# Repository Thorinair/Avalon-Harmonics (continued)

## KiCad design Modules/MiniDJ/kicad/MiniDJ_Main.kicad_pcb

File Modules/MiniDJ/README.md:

# Avalon Harmonics MiniDJ

**Stereo crossfader and DJ style filter**

MiniDJ is a compact fully analog module that houses a stereo crossfader with an adjustable volume curve, as well as a DJ style filter, both adjustable with CV. The module is compact at only 6hp and very shallow, making it an easy install in various travel and performance cases. **Features a golden (ENIG coated) panel.**

The module has two sets of stereo inputs, which correspond to channels A and B, as well as a stereo output. The two channels are mixed together through the crossfader, and are then passed into the DJ style filter before leaving the module.

Crossfader is controlled using the FADE knob. A switch just below the knob adjusts the volume curve between logarihtmic when flipped to the left or linear when flipped to the right. Logarithmic curve is more popular among DJs, while the linear curve is a more standard shape in passive crossfaders. The crossfade can also be controlled using CV through the FADE jack. An input of -5V will give 100% A channel, while an input of +5V will give 100% B channel. The FADE knob can be used as an offset when using the CV input.

Output of the crossfader is fed into the DJ style filter. The filter is based on Thomas Henry's VCF circuit, but modified to fit this use case. Cutoff is controlled using the CUT knob. The knob has a center detent for easier live performance. This is where the filter is completely open. As the knob is turned to the left, the signal gets lowpassed. As the knob is turned to the right, the signal gets highpassed. Resonances of LP and HP are controlled separately using the two RES knobs. Note that the filter itself is always active even when in neutral position, so resonance adds some coloration to the sound. Because of this, resonance knobs can be used as a sort of equalizer for the overall sound, even when the cutoff is in neutral position. Cutoff can also be controlled using CV through the CUT jack. An input of -5V will fully lowpass it, while an input of +5V will fully highpass it. Similar to the crossfader, the CUT knob can be used as an offset when using the CV input.

Finally, the module also has a set of two red LEDs which flash when clipping is expected on the output. Internally, the module halves the volume of both channels to prevent internal clipping, and then boosts it back up on output. Some clipping can occur though when mixing two loud signals together or when high resonance is involved. The LEDs help in those cases.

Visit Website: https://avalon-harmonics.com/module/MiniDJ/

### Features

* Stereo crossfader with adjustable curve
* Stereo DJ style filter
* Separate LP and HP resonances
* CV inputs for crossfader and filter
* Fully analog circuitry
* Clipping LEDs for output
* Wrong polarity protection
* Skiff friendly
* Size: 6HP
* Depth: 26mm
* Power: +12V: 93mA, -12V: 89mA

### Credits

* Filter circuit based on [Thomas Henry's VCF circuit](https://www.birthofasynth.com/Thomas_Henry/Pages/VCF-1.html)

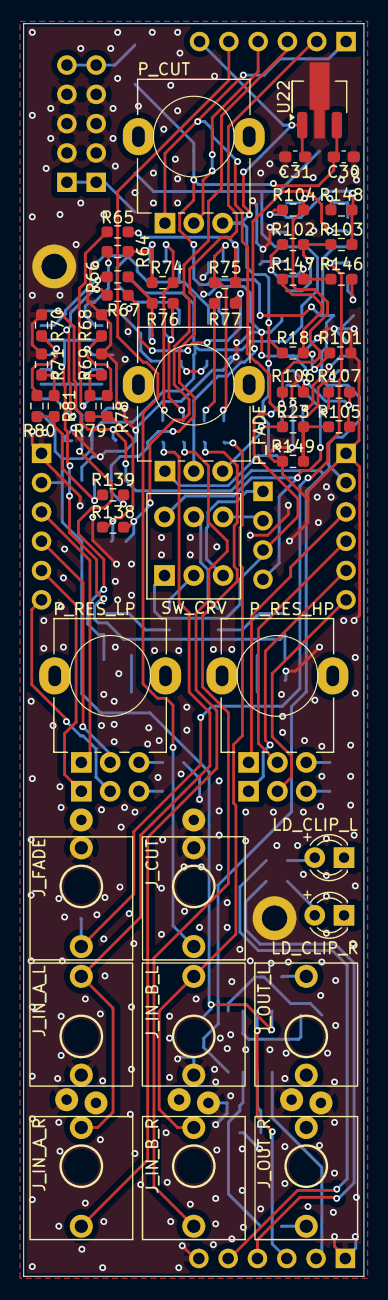
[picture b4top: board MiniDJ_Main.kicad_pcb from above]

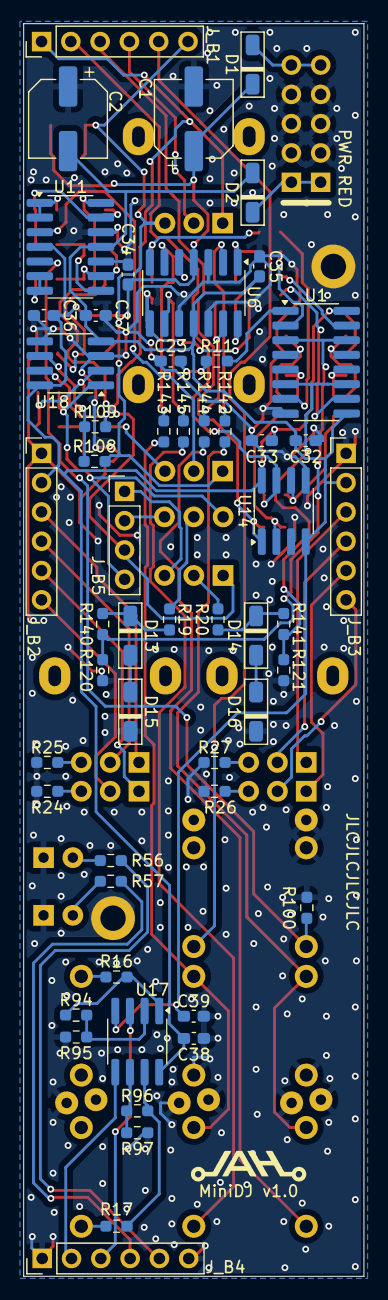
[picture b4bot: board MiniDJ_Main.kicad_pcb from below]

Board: 2 copper layers, 29.5 x 108.6 mm, 104 parts (55 on the bottom side), 82 nets.

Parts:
C1, C2: 47uF; CP_Elec_6.3x5.3
C23: 4.7nF; C_0603_1608Metric_Pad1.08x0.95mm_HandSolder
C30, C31, C32, C33, C34, C35, C36, C37, C38, C39: 0.1uF; C_0603_1608Metric_Pad1.08x0.95mm_HandSolder
D1, D2: FM4001; D_SOD-123F_AH
D13, D14: BZT52C4V3 (4.3V); D_SOD-123F_AH
D15, D16: BZT52C2V0 (2.0V); D_SOD-123F_AH
J_B1, J_B2, J_B3, J_B4: Conn_01x06_Female; PinHeader_1x06_P2.54mm_Vertical
J_B5: Conn_01x04_Female; PinHeader_1x04_P2.54mm_Vertical
J_CUT: PJ301M-12
J_FADE: PJ301M-12
J_IN_A_L: PJ301M-12; PJ301M-12 Offset
J_IN_A_R: PJ301M-12; PJ301M-12 Offset
J_IN_B_L: PJ301M-12; PJ301M-12 Offset
J_IN_B_R: PJ301M-12; PJ301M-12 Offset
J_OUT_L: PJ301M-12; PJ301M-12 Offset
J_OUT_R: PJ301M-12; PJ301M-12 Offset
LD_CLIP_L: LED; LED_D3.0mm_FlatTop
LD_CLIP_R: LED; LED_D3.0mm_FlatTop
PWR1: PWR_10_Pin; Eurorack Power 10 Pin
P_CUT: B50k; Potentiometer Alpha RD901F-40-00D
P_FADE: B100k; Potentiometer Alpha RD901F-40-00D
P_RES_HP: B50k; Potentiometer Alpha Dual RD901F-40-00D
P_RES_LP: B50k; Potentiometer Alpha Dual RD901F-40-00D
R11: 100; R_0603_1608Metric_Pad0.98x0.95mm_HandSolder
R16, R17, R18, R19, R20: 1k; R_0603_1608Metric_Pad0.98x0.95mm_HandSolder
R23: 2.7k; R_0603_1608Metric_Pad0.98x0.95mm_HandSolder
R24, R25, R26, R27: 5.6k; R_0603_1608Metric_Pad0.98x0.95mm_HandSolder
R56, R57: 22k; R_0603_1608Metric_Pad0.98x0.95mm_HandSolder
R64, R65, R66, R67, R68, R69, R70, R71: 47k; R_0603_1608Metric_Pad0.98x0.95mm_HandSolder
R74, R75, R76, R77, R78, R79, R80, R81, R94, R95, R96, R97, R100, R101, R102, R103, R104, R105, R106, R107, R108, R109, R120, R121: 100k; R_0603_1608Metric_Pad0.98x0.95mm_HandSolder
R138, R139, R140, R141: 160k; R_0603_1608Metric_Pad0.98x0.95mm_HandSolder
R142, R143, R144, R145, R146, R147, R148, R149: 200k; R_0603_1608Metric_Pad0.98x0.95mm_HandSolder
SW_CRV: SW_DPDT_x2; DPDT
U1: AS3364D; SO-16_3.9x9.9mm_P1.27mm_AH
U6, U11: TL074; SO-14_3.9x8.65mm_P1.27mm_AH
U14, U17, U18: TL072; SO-8_3.9x4.9mm_P1.27mm_AH
U22: 78L05; SOT-89-3_Handsoldering

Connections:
+5V: C31.1, J_B1.6, P_CUT.3, P_FADE.1, R18.2, R108.2, U22.1 (VO)
+12V: C1.1, C30.1, C33.2, C34.1, C36.1, C38.1, D1.1 (K), J_B2.2, U1.16 (V+), U6.4 (V+), U11.4 (V+), U14.8 (V+), U17.8 (V+), U18.8 (V+), U22.3 (VI)
-5V: J_B1.1, P_CUT.1, P_FADE.3, R23.2, R109.1, U18.7
-12V: C2.2, C32.1, C35.2, C37.2, C39.2, D2.2 (A), J_B3.2, U1.9 (V-), U6.11 (V-), U11.11 (V-), U14.4 (V-), U17.4 (V-), U18.4 (V-)
/CLIP_L_MAIN: J_B4.5, R56.2
/CLIP_R_MAIN: J_B4.4, R57.2
/FADE_A: R120.2, R140.1, U1.3, U1.14
/FADE_A_LIN: J_B5.4, R107.1, SW_CRV.4 (A), U18.1
/FADE_A_LOG: J_B5.2, SW_CRV.6 (C)
/FADE_B: R121.2, R141.1, U1.6, U1.11
/FADE_B_LIN: J_B5.3, R104.1, R106.2, SW_CRV.1 (A), U11.14
/FADE_B_LOG: J_B5.1, SW_CRV.3 (C)
/IN_CUT_MAIN: J_B1.5, J_CUT.SIG
/IN_L_A: J_IN_A_L.SIG, J_IN_A_R.SW, R142.2
/IN_L_B: J_IN_B_L.SIG, J_IN_B_R.SW, R143.2
/MIX_L_MAIN: J_B1.3, R138.1, U14.1
/MIX_R_MAIN: J_B1.2, R139.1, U14.7
/PRE_L_MAIN: J_B4.3, U17.3 (+)
/PRE_R_MAIN: J_B4.2, U17.5 (+)
/P_CUT_MAIN: J_B1.4, P_CUT.2
/RES_HP_L_1_MAIN: J_B2.3, P_RES_HP.1
/RES_HP_L_2_MAIN: J_B2.4, P_RES_HP.2
/RES_HP_R_1_MAIN: J_B2.5, P_RES_HP.4
/RES_HP_R_2_MAIN: J_B2.6, P_RES_HP.5
/RES_LP_L_1_MAIN: J_B3.3, P_RES_LP.1
/RES_LP_L_2_MAIN: J_B3.4, P_RES_LP.2
/RES_LP_R_1_MAIN: J_B3.5, P_RES_LP.4
/RES_LP_R_2_MAIN: J_B3.6, P_RES_LP.5
GND: C1.2, C2.1, C23.2, C30.2, C31.2, C32.2, C33.1, C34.2, C35.1, C36.2, C37.1, C38.2, C39.1, D15.1 (K), D16.1 (K), J_B2.1, J_B3.1, J_B4.1, J_B4.6, J_CUT.GND, J_CUT.SW, J_FADE.GND, J_FADE.SW, J_IN_A_L.GND, J_IN_A_L.SW, J_IN_A_R.GND, J_IN_B_L.GND, J_IN_B_L.SW, J_IN_B_R.GND, J_OUT_L.GND, J_OUT_R.GND, LD_CLIP_L.1 (K), LD_CLIP_R.1 (K), PWR1.2 (GND), R24.1, R25.1, R26.1, R27.1, R68.1, R69.1, R70.1, R71.1, R95.1, R97.1, R100.1, R101.1, R120.1, R121.1, R149.1, U1.8 (GND), U6.3 (+), U6.5 (+), U6.10 (+), U6.12 (+), U11.10 (+), U11.12 (+), U14.3 (+), U14.5 (+), U18.3 (+), U18.5 (+), U22.2 (GND)
unnamed: C23.1, R11.2
unnamed: D1.2 (A), PWR1.1 (+12V)
unnamed: D2.1 (K), PWR1.3 (-12V)
unnamed: D13.2 (A), D15.2 (A)
unnamed: D13.1 (K), R19.1, R140.2
unnamed: D14.2 (A), D16.2 (A)
unnamed: D14.1 (K), R20.1, R141.2
unnamed: J_IN_A_R.SIG, R144.2
unnamed: J_IN_B_R.SIG, R145.2
unnamed: J_OUT_L.SIG, R16.1
unnamed: J_OUT_R.SIG, R17.1
unnamed: LD_CLIP_L.2 (A), R56.1
unnamed: LD_CLIP_R.2 (A), R57.1
unnamed: P_RES_HP.3, R25.2
unnamed: P_RES_HP.6, R24.2
unnamed: P_RES_LP.3, R27.2
unnamed: P_RES_LP.6, R26.2
unnamed: R16.2, R94.1, U17.1
unnamed: R17.2, R96.1, U17.7
unnamed: R64.1, U1.2
unnamed: R64.2, R74.1, U6.1
unnamed: R65.1, U1.7
unnamed: R65.2, R75.1, U6.7
unnamed: R66.1, U1.15
unnamed: R66.2, R76.1, U6.14
unnamed: R67.1, U1.10
unnamed: R67.2, R77.1, U6.8
unnamed: R68.2, R78.2, U1.4
unnamed: R69.2, R79.2, U1.5
unnamed: R70.2, R80.2, U1.13
unnamed: R71.2, R81.2, U1.12
unnamed: R18.1, R101.2, R147.2
unnamed: R102.1, R103.2, U11.8
unnamed: R23.1, R105.2, R149.2
unnamed: R20.2, SW_CRV.2 (B)
unnamed: R19.2, SW_CRV.5 (B)
unnamed: R11.1, U1.1 (Vref)
unnamed: R74.2, R142.1, U6.2 (-)
unnamed: R75.2, R143.1, U6.6 (-)
unnamed: R77.2, R145.1, U6.9 (-)
unnamed: R76.2, R144.1, U6.13 (-)
unnamed: P_FADE.2, U11.3 (+)
unnamed: R148.2, U11.1, U11.2 (-)
unnamed: J_FADE.SIG, R100.2, U11.5 (+)
unnamed: R146.2, U11.6 (-), U11.7
unnamed: R102.2, R146.1, R147.1, U11.9 (-)
unnamed: R103.1, R104.2, R148.1, U11.13 (-)
unnamed: R78.1, R79.1, R138.2, U14.2 (-)
unnamed: R80.1, R81.1, R139.2, U14.6 (-)
unnamed: R94.2, R95.2, U17.2 (-)
unnamed: R96.2, R97.2, U17.6 (-)
unnamed: R105.1, R106.1, R107.2, U18.2 (-)
unnamed: R108.1, R109.2, U18.6 (-)

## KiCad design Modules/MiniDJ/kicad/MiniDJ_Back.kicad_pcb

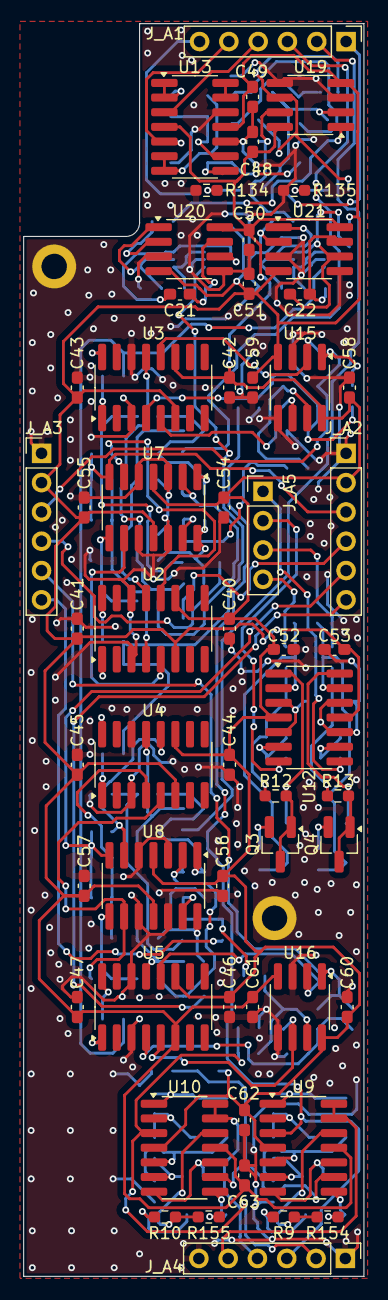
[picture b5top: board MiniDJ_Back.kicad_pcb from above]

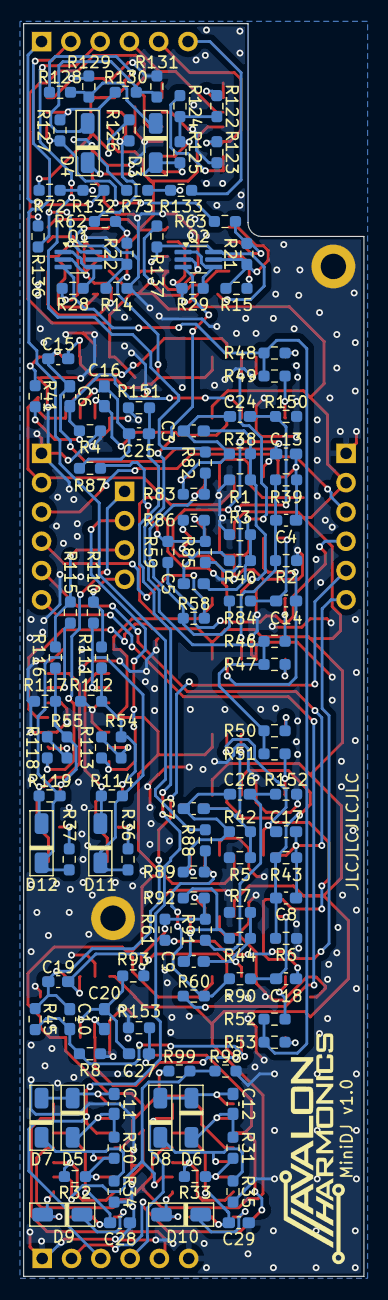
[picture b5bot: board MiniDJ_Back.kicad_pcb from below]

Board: 2 copper layers, 29.5 x 108.6 mm, 182 parts (126 on the bottom side), 115 nets.

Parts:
C3, C4, C5, C6, C7, C8, C9, C10: 10pF; C_0603_1608Metric_Pad1.08x0.95mm_HandSolder
C11, C12: 47pF; C_0603_1608Metric_Pad1.08x0.95mm_HandSolder
C13, C14, C15, C16, C17, C18, C19, C20: 330pF; C_0603_1608Metric_Pad1.08x0.95mm_HandSolder
C21, C22: 1nF; C_0603_1608Metric_Pad1.08x0.95mm_HandSolder
C24, C25, C26, C27, C28, C29, C40, C41, C42, C43, C44, C45, C46, C47, C48, C49, C50, C51, C52, C53, C54, C55, C56, C57, C58, C59, C60, C61, C62, C63: 0.1uF; C_0603_1608Metric_Pad1.08x0.95mm_HandSolder
D3, D4, D5, D6, D7, D8, D9, D10, D11, D12: 1N4148W; D_SOD-123F_AH
J_A1, J_A2, J_A3, J_A4: Conn_01x06_Male; PinHeader_1x06_P2.54mm_Vertical
J_A5: Conn_01x04_Male; PinHeader_1x04_P2.54mm_Vertical
Q1, Q2: BCM857BS; SOT-363_SC-70-6_Handsoldering
Q3, Q4: MMBT3906; SOT-23_Handsoldering
R1, R2, R3, R4, R5, R6, R7, R8: 22; R_0603_1608Metric_Pad0.98x0.95mm_HandSolder
R9, R10: 100; R_0603_1608Metric_Pad0.98x0.95mm_HandSolder
R12, R13: 220; R_0603_1608Metric_Pad0.98x0.95mm_HandSolder
R14, R15: 470; R_0603_1608Metric_Pad0.98x0.95mm_HandSolder
R21, R22: 2k; R_0603_1608Metric_Pad0.98x0.95mm_HandSolder
R28, R29: 5.6k; R_0603_1608Metric_Pad0.98x0.95mm_HandSolder
R30, R31, R32, R33, R34, R35, R36, R37: 10k; R_0603_1608Metric_Pad0.98x0.95mm_HandSolder
R38, R39, R40, R41, R42, R43, R44, R45: 11k; R_0603_1608Metric_Pad0.98x0.95mm_HandSolder
R46, R47, R48, R49, R50, R51, R52, R53, R54, R55: 15k; R_0603_1608Metric_Pad0.98x0.95mm_HandSolder
R58, R59, R60, R61: 27k; R_0603_1608Metric_Pad0.98x0.95mm_HandSolder
R62, R63: 47k; R_0603_1608Metric_Pad0.98x0.95mm_HandSolder
R72, R73: 68k; R_0603_1608Metric_Pad0.98x0.95mm_HandSolder
R82, R83, R84, R85, R86, R87, R88, R89, R90, R91, R92, R93, R98, R99, R110, R111, R112, R113, R114, R115, R116, R117, R118, R119, R122, R123, R124, R125, R126, R127, R128, R129, R130, R131, R132, R133, R134, R135, R136, R137: 100k; R_0603_1608Metric_Pad0.98x0.95mm_HandSolder
R150, R151, R152, R153: 240k; R_0603_1608Metric_Pad0.98x0.95mm_HandSolder
R154, R155: 1M; R_0603_1608Metric_Pad0.98x0.95mm_HandSolder
U2, U3, U4, U5: LM13700; SO-16_3.9x9.9mm_P1.27mm_AH
U7, U8, U9, U10, U12, U13: TL074; SO-14_3.9x8.65mm_P1.27mm_AH
U15, U16, U19, U20, U21: TL072; SO-8_3.9x4.9mm_P1.27mm_AH

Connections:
+5V: J_A1.6, R133.2
+12V: C40.1, C42.1, C44.1, C46.1, C48.1, C50.1, C52.1, C54.1, C56.1, C58.1, C60.1, C62.1, J_A2.2, R99.1, U2.11 (V+), U3.11 (V+), U4.11 (V+), U5.11 (V+), U7.4 (V+), U8.4 (V+), U9.4 (V+), U10.4 (V+), U12.4 (V+), U13.4 (V+), U15.8 (V+), U16.8 (V+), U19.8 (V+), U20.8 (V+), U21.8 (V+)
-5V: J_A1.1, R132.2
-12V: C41.2, C43.2, C45.2, C47.2, C49.2, C51.2, C53.2, C55.2, C57.2, C59.2, C61.2, C63.2, J_A3.2, R136.1, R137.1, U2.6 (V-), U3.6 (V-), U4.6 (V-), U5.6 (V-), U7.11 (V-), U8.11 (V-), U9.11 (V-), U10.11 (V-), U12.11 (V-), U13.11 (V-), U15.4 (V-), U16.4 (V-), U19.4 (V-), U20.4 (V-), U21.4 (V-)
/CLIP_L_BACK: J_A4.5, U9.13 (-), U9.14
/CLIP_R_BACK: J_A4.4, U10.13 (-), U10.14
/CTRL_HP: Q2.3 (C2), R46.1, R47.1, R50.1, R51.1
/CTRL_LP: Q1.3 (C2), R48.1, R49.1, R52.1, R53.1
/CUT_HP: R63.2, R127.1, U19.1
/CUT_LP: R62.2, R126.1, U19.7
/CUT_MIX: D3.2 (A), D4.1 (K), R125.1, U13.8
/FADE_A_LIN_BACK: J_A5.4, R110.2, R111.2
/FADE_A_LOG_BACK: J_A5.2, R113.1, U12.7
/FADE_B_LIN_BACK: J_A5.3, R115.2, R116.2
/FADE_B_LOG_BACK: J_A5.1, R118.1, U12.8
/HP_L: C3.1, C24.1, R38.2, R83.1, U7.1
/HP_R: C7.1, C26.1, R42.2, R89.1, U8.1
/IN_CUT_BACK: J_A1.5, R123.2, U13.5 (+)
/MIX_L_BACK: J_A1.3, R82.2
/MIX_R_BACK: J_A1.2, R88.2
/PRE_L_BACK: C25.2, J_A4.3, R151.2, U9.3 (+)
/PRE_R_BACK: C27.2, J_A4.2, R153.2, U10.3 (+)
/P_CUT_BACK: J_A1.4, U13.3 (+)
/RES_HP_L_1_BACK: C4.1, C13.2, J_A2.3, R39.2, U7.7
/RES_HP_L_2_BACK: J_A2.4, R58.2
/RES_HP_R_1_BACK: C8.1, C17.2, J_A2.5, R43.2, U8.7
/RES_HP_R_2_BACK: J_A2.6, R60.2
/RES_LP_L_1_BACK: C6.1, C15.2, J_A3.3, R41.2, U15.1
/RES_LP_L_2_BACK: J_A3.4, R59.2
/RES_LP_R_1_BACK: C10.1, C19.2, J_A3.5, R45.2, U16.1
/RES_LP_R_2_BACK: J_A3.6, R61.2
GND: C28.1, C29.1, C40.2, C41.1, C42.2, C43.1, C44.2, C45.1, C46.2, C47.1, C48.2, C49.1, C50.2, C51.1, C52.2, C53.1, C54.2, C55.1, C56.2, C57.1, C58.2, C59.1, C60.2, C61.1, C62.2, C63.1, J_A2.1, J_A3.1, J_A4.1, J_A4.6, Q1.2 (B1), Q2.2 (B1), R1.1, R2.1, R3.1, R4.1, R5.1, R6.1, R7.1, R8.1, R14.1, R15.1, R34.1, R35.1, R98.2, R112.1, R117.1, R123.1, R129.1, R131.1, R134.1, R135.1, R150.1, R151.1, R152.1, R153.1, U2.3 (+), U2.14 (+), U3.3 (+), U3.14 (+), U4.3 (+), U4.14 (+), U5.3 (+), U5.14 (+), U7.3 (+), U7.5 (+), U7.10 (+), U7.12 (+), U8.3 (+), U8.5 (+), U8.10 (+), U8.12 (+), U12.3 (+), U12.5 (+), U12.10 (+), U12.12 (+), U13.10 (+), U13.12 (+), U15.3 (+), U15.5 (+), U16.3 (+), U16.5 (+), U19.3 (+), U19.5 (+), U20.3 (+), U20.5 (+), U21.3 (+), U21.5 (+)
unnamed: C5.1, R40.2, R86.1, U7.14
unnamed: C9.1, R44.2, R92.1, U8.14
unnamed: C14.2, R84.1, U7.8
unnamed: C16.2, C25.1, R87.1, U15.7
unnamed: C18.2, R90.1, U8.8
unnamed: C20.2, C27.1, R93.1, U16.7
unnamed: C21.2, R29.1, U20.7
unnamed: C22.2, R28.1, U21.7
unnamed: C24.2, R85.2, R150.2
unnamed: C26.2, R91.2, R152.2
unnamed: D3.1 (K), R128.2, R129.2
unnamed: D4.2 (A), R130.2, R131.2
unnamed: C11.2, D5.2 (A), R30.2, U9.2 (-)
unnamed: C11.1, D5.1 (K), D7.2 (A), U9.1
unnamed: C12.2, D6.2 (A), R31.2, U10.2 (-)
unnamed: C12.1, D6.1 (K), D8.2 (A), U10.1
unnamed: D7.1 (K), R34.2, U9.5 (+)
unnamed: D8.1 (K), R35.2, U10.5 (+)
unnamed: D9.2 (A), R154.2, U9.8
unnamed: D9.1 (K), R9.2
unnamed: D10.2 (A), R155.2, U10.8
unnamed: D10.1 (K), R10.2
unnamed: D11.2 (A), Q3.1 (B), Q3.3 (C), R12.2, R114.1, U12.1
unnamed: D11.1 (K), R36.2, R110.1, R114.2, U12.2 (-)
unnamed: D12.2 (A), Q4.1 (B), Q4.3 (C), R13.2, R119.1, U12.14
unnamed: D12.1 (K), R37.2, R115.1, R119.2, U12.13 (-)
unnamed: C22.1, Q1.6 (C1), R136.2, U21.6 (-)
unnamed: Q1.1 (E1), Q1.4 (E2), R28.2
unnamed: Q1.5 (B2), R14.2, R22.1, U21.1
unnamed: C21.1, Q2.6 (C1), R137.2, U20.6 (-)
unnamed: Q2.1 (E1), Q2.4 (E2), R29.2
unnamed: Q2.5 (B2), R15.2, R21.1, U20.1
unnamed: Q3.2 (E), R36.1
unnamed: Q4.2 (E), R37.1
unnamed: R46.2, U2.16
unnamed: R47.2, U2.1
unnamed: R48.2, U3.16
unnamed: R49.2, U3.1
unnamed: R50.2, U4.16
unnamed: R51.2, U4.1
unnamed: R52.2, U5.16
unnamed: R53.2, U5.1
unnamed: R12.1, R54.2, R111.1, R112.2
unnamed: R13.1, R55.2, R116.1, R117.2
unnamed: R72.2, R132.1, R135.2
unnamed: R73.2, R133.1, R134.2
unnamed: C3.2, R1.2, R38.1, U2.13 (-)
unnamed: C4.2, R2.2, R39.1, U2.4 (-)
unnamed: C5.2, R3.2, R40.1, U3.13 (-)
unnamed: C6.2, R4.2, R41.1, U3.4 (-)
unnamed: C7.2, R5.2, R42.1, U4.13 (-)
unnamed: C8.2, R6.2, R43.1, U4.4 (-)
unnamed: C9.2, R7.2, R44.1, U5.13 (-)
unnamed: C10.2, R8.2, R45.1, U5.4 (-)
unnamed: R58.1, R82.1, R83.2, R84.2, U7.2 (-)
unnamed: C13.1, U2.12, U7.6 (-)
unnamed: C14.1, U2.5, U7.9 (-)
unnamed: R59.1, R85.1, R86.2, R87.2, U7.13 (-)
unnamed: R60.1, R88.1, R89.2, R90.2, U8.2 (-)
unnamed: C17.1, U4.12, U8.6 (-)
unnamed: C18.1, U4.5, U8.9 (-)
unnamed: R61.1, R91.1, R92.2, R93.2, U8.13 (-)
unnamed: R30.1, R32.2, U9.6 (-)
unnamed: R32.1, U9.7, U9.10 (+)
unnamed: C28.2, R9.1, R154.1, U9.12 (+)
unnamed: R31.1, R33.2, U10.6 (-)
unnamed: R33.1, U10.7, U10.10 (+)
unnamed: R98.1, R99.2, U9.9 (-), U10.9 (-)
unnamed: C29.2, R10.1, R155.1, U10.12 (+)
unnamed: R54.1, R113.2, U12.6 (-)
unnamed: R55.1, R118.2, U12.9 (-)
unnamed: R122.2, U13.1, U13.2 (-)
unnamed: R124.2, U13.6 (-), U13.7
unnamed: R122.1, R124.1, R125.2, U13.9 (-)
unnamed: U13.13 (-), U13.14
unnamed: C15.1, U3.12, U15.2 (-)
unnamed: C16.1, U3.5, U15.6 (-)
unnamed: C19.1, U5.12, U16.2 (-)
unnamed: C20.1, U5.5, U16.6 (-)
unnamed: R73.1, R127.2, R130.1, U19.2 (-)
unnamed: R72.1, R126.2, R128.1, U19.6 (-)
unnamed: R21.2, R63.1, U20.2 (-)
unnamed: R22.2, R62.1, U21.2 (-)

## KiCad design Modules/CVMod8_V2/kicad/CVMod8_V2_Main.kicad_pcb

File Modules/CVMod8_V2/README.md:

# Avalon Harmonics CVMod8 V2

**8 channel CV attenuverter, offset and mixer**

Now comes as an SMD module. **Features a golden (ENIG coated) panel.** THT version has been discontinued.

CVMod8 V2 is successor to the old CVMod8. The module provides 8 channels of independent CV attenuverters and offset controls, as well as offset polarity switches and forward switches for mixing the channels together.

Each channel can be used as a static voltage source with the output available on the top-most row of jacks. Sliders control the voltage, and the voltage can be bipolar (+5V to -5V) or unipolar (+5V to 0V) by flipping the corresponding switch on the bottom. Behavior is bipolar when switched to the left and unipolar when switched to the right. Internally, voltage regulators ensure a precise voltage source. Note that there is a 5V spike when switching the polarity.

Each channel also has a signal input (second row of jacks) with a corresponding attenuverter knob below. The knobs have a centre detent as this is where the input gain is set to 0. When turned clockwise, level of the signal can be adjusted up to unity gain. When turned counter-clockwise, signal gets inverted up to a negative unity gain. The input signal is mixed together with the previously mentioned slider value, allowing the sliders to offset the incoming signal.

Output of each channel can be forwarded to the next channel by flipping a corresponding switch to the right in the upper row of switches. The signal is then mixed together with the attenuverted CV and offset of the next channel. Each channel has the following formula:

`output = input * attenuverter + offset + output_prev`

* `input` is whatever signal is plugged into the second row jack.
* `attenuverter` is the position of the attenuverter knob and can range from -1 to 1.
* `offset` is the offset voltage set by the slider and polarity switch. Can range from +5V to -5V or 5V to 0V.
* `output_prev` is the output signal from the previous channel, if the forwarding switch has been flipped.

The forwarding feature can be used to chain multiple channels together acting as a CV mixer with outputs still available on each channel. Plugging a cable into one of the outputs does not interrupt the forwarding, so it is possible to make use of submixes. If a need arises for an audio mixer, setting offsets to unipolar mode and sliding them all the way down will achieve this kind of behavior.

Lastly, a bipolar LED exists for each channel as a clear indicator of the status of the output voltage.

**Differences compared to the old CVMod8:**

* Attenuverters instead of normal attenuators, allowing for inverting signals.
* Easier finger access to the knobs as jacks are no longer in the way.
* More precise offset voltages using voltage regulators and buffering before mixing.
* Offset polarity toggles as accessible switches on the bottom.
* Forwarding of channels as accessible switches on the top.
* Visually a better fit of the slider knobs.
* For DIY-ers, easier to obtain slide pots and no more need for the 3D printed interface part.
* NOTE: More parts required the module to be around 10mm deeper and use more current.

Visit Website: https://avalon-harmonics.com/module/CVMod8_V2/

### Features

* 8 independent channels
* Offset for each channel with a polarity switch
* Each channel with an input and attenuverter
* Togglable forwarding of outputs to next channel
* Status LEDs for each channel
* Wrong polarity protection
* Skiff friendly
* Size: 20HP
* Depth: 25mm  (36mm THT)
* Power: +12V: 115mA, -12V: 104mA (+12V: 123mA, -12V: 111mA THT)

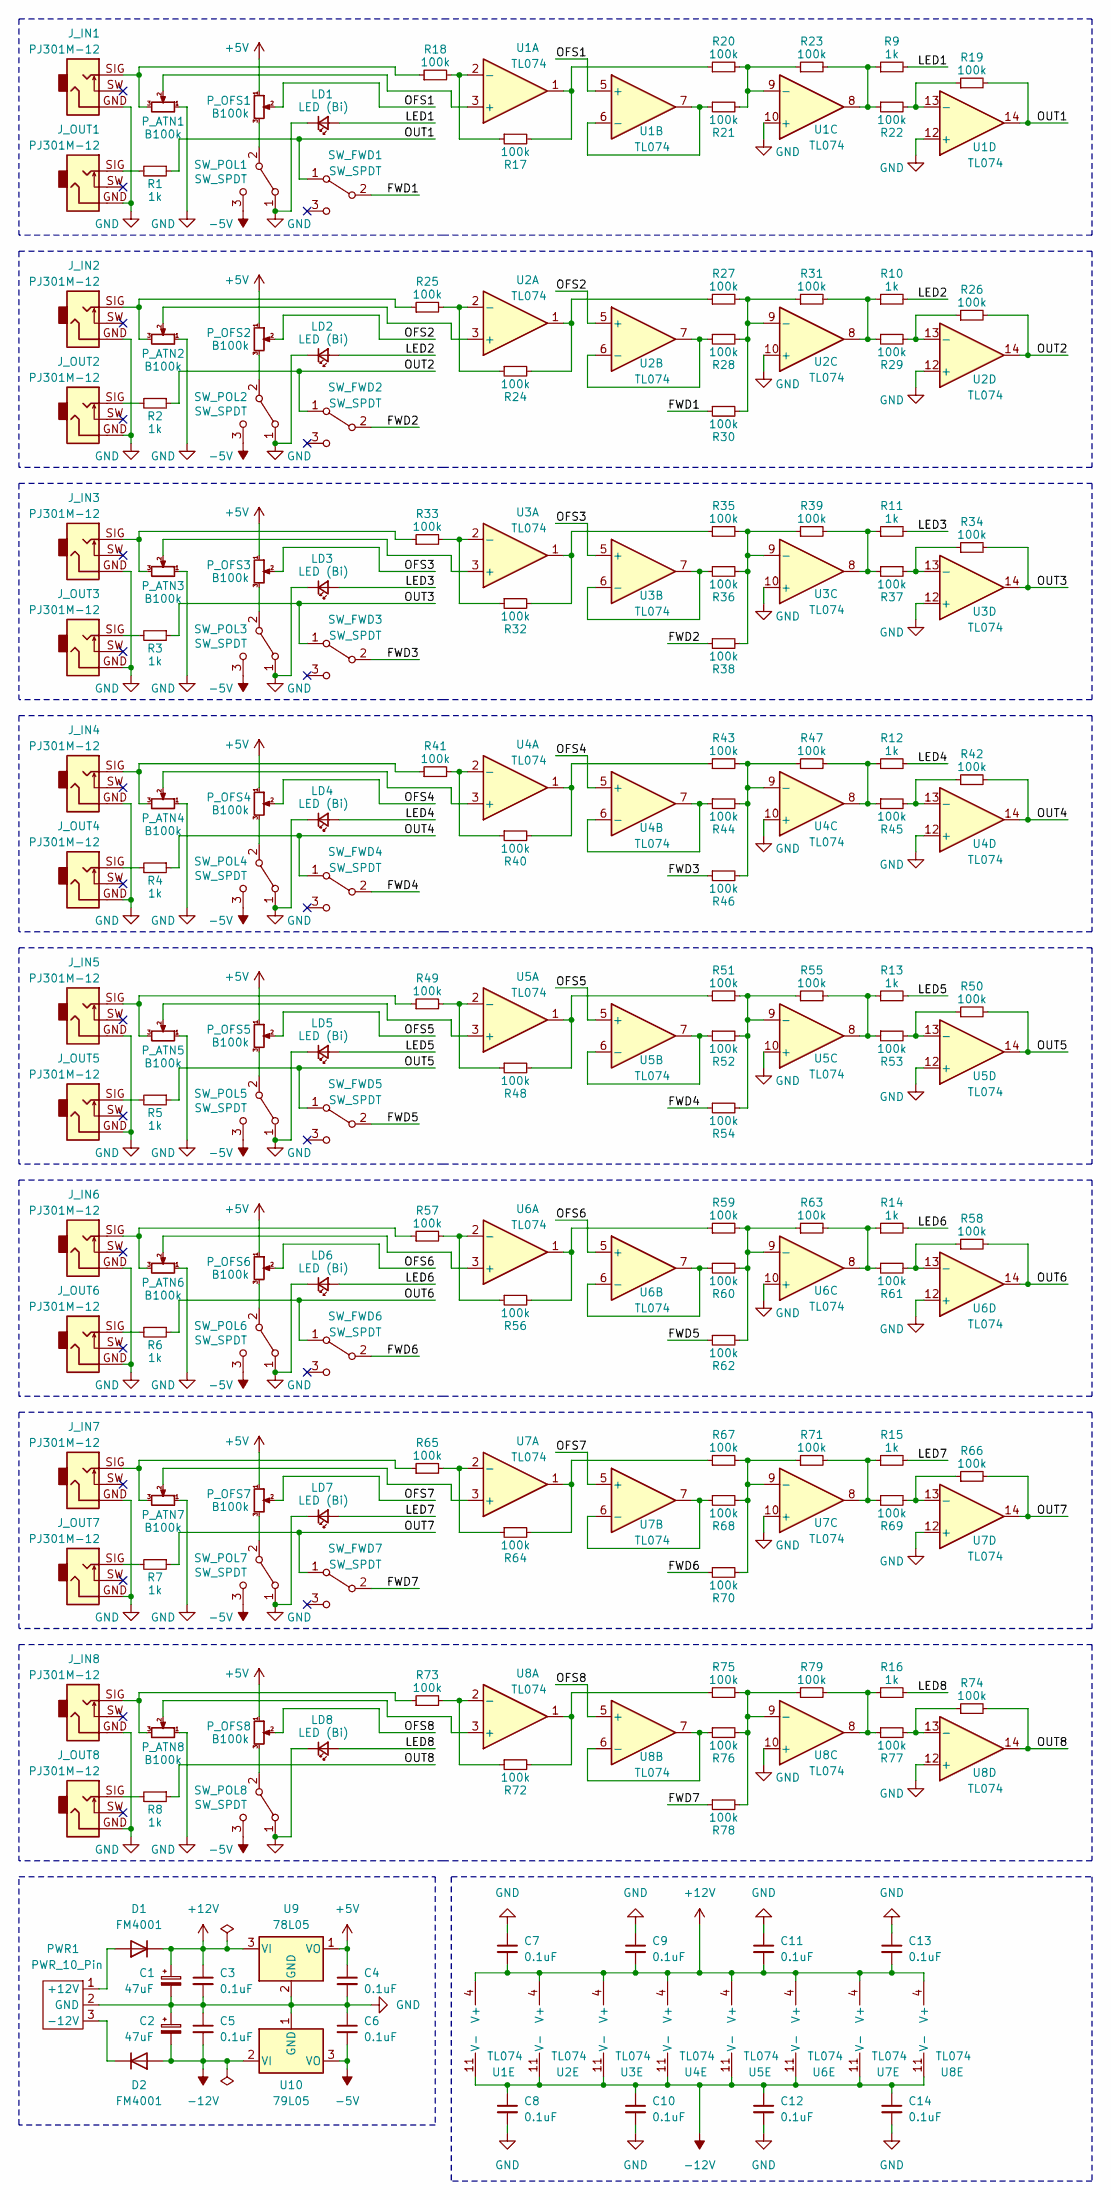
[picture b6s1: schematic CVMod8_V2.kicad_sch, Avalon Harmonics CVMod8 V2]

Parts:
C1, C2: 47uF; CP_Elec_6.3x5.3
C3, C4, C5, C6, C7, C8, C9, C10, C11, C12, C13, C14: 0.1uF; C_0603_1608Metric_Pad1.08x0.95mm_HandSolder
D1, D2: FM4001; D_SOD-123F_AH
J_IN1, J_IN2, J_IN3, J_IN4, J_IN5, J_IN6, J_IN7, J_IN8: PJ301M-12; PJ301M-12 Offset
J_OUT1, J_OUT2, J_OUT3, J_OUT4, J_OUT5, J_OUT6, J_OUT7, J_OUT8: PJ301M-12; PJ301M-12 Offset
LD1, LD2, LD3, LD4, LD5, LD6, LD7, LD8: LED (Bi); LED_D3.0mm_FlatTop
PWR1: PWR_10_Pin; Eurorack Power 10 Pin
P_ATN1, P_ATN2, P_ATN3, P_ATN4, P_ATN5, P_ATN6, P_ATN7, P_ATN8: B100k; Potentiometer Song Huei 9mm Trimmer
P_OFS1, P_OFS2, P_OFS3, P_OFS4, P_OFS5, P_OFS6, P_OFS7, P_OFS8: B100k; Potentiometer_Bourns_PTA3043_Single_Slide
R1, R2, R3, R4, R5, R6, R7, R8, R9, R10, R11, R12, R13, R14, R15, R16: 1k; R_0603_1608Metric_Pad0.98x0.95mm_HandSolder
R17, R18, R19, R20, R21, R22, R23, R24, R25, R26, R27, R28, R29, R30, R31, R32, R33, R34, R35, R36, R37, R38, R39, R40, R41, R42, R43, R44, R45, R46, R47, R48, R49, R50, R51, R52, R53, R54, R55, R56, R57, R58, R59, R60, R61, R62, R63, R64, R65, R66, R67, R68, R69, R70, R71, R72, R73, R74, R75, R76, R77, R78, R79: 100k; R_0603_1608Metric_Pad0.98x0.95mm_HandSolder
SW_FWD1, SW_FWD2, SW_FWD3, SW_FWD4, SW_FWD5, SW_FWD6, SW_FWD7: SW_SPDT; SPDT
SW_POL1, SW_POL2, SW_POL3, SW_POL4, SW_POL5, SW_POL6, SW_POL7, SW_POL8: SW_SPDT; SPDT
U1, U2, U3, U4, U5, U6, U7, U8: TL074; SO-14_3.9x8.65mm_P1.27mm_AH
U9: 78L05; SOT-89-3_Handsoldering
U10: 79L05; SOT-89-3_Handsoldering

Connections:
+5V: C4.1, P_OFS1.1, P_OFS2.1, P_OFS3.1, P_OFS4.1, P_OFS5.1, P_OFS6.1, P_OFS7.1, P_OFS8.1, U9.1 (VO)
+12V: C1.1, C3.1, C7.2, C9.2, C11.2, C13.2, D1.1 (K), U1.4 (V+), U2.4 (V+), U3.4 (V+), U4.4 (V+), U5.4 (V+), U6.4 (V+), U7.4 (V+), U8.4 (V+), U9.3 (VI)
-5V: C6.2, SW_POL1.3 (C), SW_POL2.3 (C), SW_POL3.3 (C), SW_POL4.3 (C), SW_POL5.3 (C), SW_POL6.3 (C), SW_POL7.3 (C), SW_POL8.3 (C), U10.3 (VO)
-12V: C2.2, C5.2, C8.1, C10.1, C12.1, C14.1, D2.2 (A), U1.11 (V-), U2.11 (V-), U3.11 (V-), U4.11 (V-), U5.11 (V-), U6.11 (V-), U7.11 (V-), U8.11 (V-), U10.2 (VI)
/FWD1: R30.1, SW_FWD1.2 (B)
/FWD2: R38.1, SW_FWD2.2 (B)
/FWD3: R46.1, SW_FWD3.2 (B)
/FWD4: R54.1, SW_FWD4.2 (B)
/FWD5: R62.1, SW_FWD5.2 (B)
/FWD6: R70.1, SW_FWD6.2 (B)
/FWD7: R78.1, SW_FWD7.2 (B)
/LED1: LD1.2 (A), R9.2
/LED2: LD2.2 (A), R10.2
/LED3: LD3.2 (A), R11.2
/LED4: LD4.2 (A), R12.2
/LED5: LD5.2 (A), R13.2
/LED6: LD6.2 (A), R14.2
/LED7: LD7.2 (A), R15.2
/LED8: LD8.2 (A), R16.2
/OFS1: P_OFS1.2, U1.5 (+)
/OFS2: P_OFS2.2, U2.5 (+)
/OFS3: P_OFS3.2, U3.5 (+)
/OFS4: P_OFS4.2, U4.5 (+)
/OFS5: P_OFS5.2, U5.5 (+)
/OFS6: P_OFS6.2, U6.5 (+)
/OFS7: P_OFS7.2, U7.5 (+)
/OFS8: P_OFS8.2, U8.5 (+)
/OUT1: R1.1, R19.2, SW_FWD1.1 (A), U1.14
/OUT2: R2.1, R26.2, SW_FWD2.1 (A), U2.14
/OUT3: R3.1, R34.2, SW_FWD3.1 (A), U3.14
/OUT4: R4.1, R42.2, SW_FWD4.1 (A), U4.14
/OUT5: R5.1, R50.2, SW_FWD5.1 (A), U5.14
/OUT6: R6.1, R58.2, SW_FWD6.1 (A), U6.14
/OUT7: R7.1, R66.2, SW_FWD7.1 (A), U7.14
/OUT8: R8.1, R74.2, U8.14
GND: C1.2, C2.1, C3.2, C4.2, C5.1, C6.1, C7.1, C8.2, C9.1, C10.2, C11.1, C12.2, C13.1, C14.2, J_IN1.GND, J_IN2.GND, J_IN3.GND, J_IN4.GND, J_IN5.GND, J_IN6.GND, J_IN7.GND, J_IN8.GND, J_OUT1.GND, J_OUT2.GND, J_OUT3.GND, J_OUT4.GND, J_OUT5.GND, J_OUT6.GND, J_OUT7.GND, J_OUT8.GND, LD1.1 (K), LD2.1 (K), LD3.1 (K), LD4.1 (K), LD5.1 (K), LD6.1 (K), LD7.1 (K), LD8.1 (K), PWR1.2 (GND), P_ATN1.1, P_ATN2.1, P_ATN3.1, P_ATN4.1, P_ATN5.1, P_ATN6.1, P_ATN7.1, P_ATN8.1, SW_POL1.1 (A), SW_POL2.1 (A), SW_POL3.1 (A), SW_POL4.1 (A), SW_POL5.1 (A), SW_POL6.1 (A), SW_POL7.1 (A), SW_POL8.1 (A), U1.10 (+), U1.12 (+), U2.10 (+), U2.12 (+), U3.10 (+), U3.12 (+), U4.10 (+), U4.12 (+), U5.10 (+), U5.12 (+), U6.10 (+), U6.12 (+), U7.10 (+), U7.12 (+), U8.10 (+), U8.12 (+), U9.2 (GND), U10.1 (GND)
unnamed: D1.2 (A), PWR1.1 (+12V)
unnamed: D2.1 (K), PWR1.3 (-12V)
unnamed: J_IN1.SIG, P_ATN1.3, R18.1
unnamed: J_IN2.SIG, P_ATN2.3, R25.1
unnamed: J_IN3.SIG, P_ATN3.3, R33.1
unnamed: J_IN4.SIG, P_ATN4.3, R41.1
unnamed: J_IN5.SIG, P_ATN5.3, R49.1
unnamed: J_IN6.SIG, P_ATN6.3, R57.1
unnamed: J_IN7.SIG, P_ATN7.3, R65.1
unnamed: J_IN8.SIG, P_ATN8.3, R73.1
unnamed: J_OUT1.SIG, R1.2
unnamed: J_OUT2.SIG, R2.2
unnamed: J_OUT3.SIG, R3.2
unnamed: J_OUT4.SIG, R4.2
unnamed: J_OUT5.SIG, R5.2
unnamed: J_OUT6.SIG, R6.2
unnamed: J_OUT7.SIG, R7.2
unnamed: J_OUT8.SIG, R8.2
unnamed: R10.1, R29.1, R31.2, U2.8
unnamed: R11.1, R37.1, R39.2, U3.8
unnamed: R12.1, R45.1, R47.2, U4.8
unnamed: R13.1, R53.1, R55.2, U5.8
unnamed: R14.1, R61.1, R63.2, U6.8
unnamed: R15.1, R69.1, R71.2, U7.8
unnamed: R16.1, R77.1, R79.2, U8.8
unnamed: R17.2, R20.1, U1.1
unnamed: R9.1, R22.1, R23.2, U1.8
unnamed: R24.2, R27.1, U2.1
unnamed: R32.2, R35.1, U3.1
unnamed: R40.2, R43.1, U4.1
unnamed: R48.2, R51.1, U5.1
unnamed: R56.2, R59.1, U6.1
unnamed: R64.2, R67.1, U7.1
unnamed: R72.2, R75.1, U8.1
unnamed: P_OFS1.3, SW_POL1.2 (B)
unnamed: P_OFS2.3, SW_POL2.2 (B)
unnamed: P_OFS3.3, SW_POL3.2 (B)
unnamed: P_OFS4.3, SW_POL4.2 (B)
unnamed: P_OFS5.3, SW_POL5.2 (B)
unnamed: P_OFS6.3, SW_POL6.2 (B)
unnamed: P_OFS7.3, SW_POL7.2 (B)
unnamed: P_OFS8.3, SW_POL8.2 (B)
unnamed: P_ATN1.2, U1.3 (+)
unnamed: R17.1, R18.2, U1.2 (-)
unnamed: R21.1, U1.6 (-), U1.7
unnamed: R20.2, R21.2, R23.1, U1.9 (-)
unnamed: R19.1, R22.2, U1.13 (-)
unnamed: P_ATN2.2, U2.3 (+)
unnamed: R24.1, R25.2, U2.2 (-)
unnamed: R28.1, U2.6 (-), U2.7
unnamed: R27.2, R28.2, R30.2, R31.1, U2.9 (-)
unnamed: R26.1, R29.2, U2.13 (-)
unnamed: P_ATN3.2, U3.3 (+)
unnamed: R32.1, R33.2, U3.2 (-)
unnamed: R36.1, U3.6 (-), U3.7
unnamed: R35.2, R36.2, R38.2, R39.1, U3.9 (-)
unnamed: R34.1, R37.2, U3.13 (-)
unnamed: P_ATN4.2, U4.3 (+)
unnamed: R40.1, R41.2, U4.2 (-)
unnamed: R44.1, U4.6 (-), U4.7
unnamed: R43.2, R44.2, R46.2, R47.1, U4.9 (-)
unnamed: R42.1, R45.2, U4.13 (-)
unnamed: P_ATN5.2, U5.3 (+)
unnamed: R48.1, R49.2, U5.2 (-)
unnamed: R52.1, U5.6 (-), U5.7
unnamed: R51.2, R52.2, R54.2, R55.1, U5.9 (-)
unnamed: R50.1, R53.2, U5.13 (-)
unnamed: P_ATN6.2, U6.3 (+)
unnamed: R56.1, R57.2, U6.2 (-)
unnamed: R60.1, U6.6 (-), U6.7
unnamed: R59.2, R60.2, R62.2, R63.1, U6.9 (-)
unnamed: R58.1, R61.2, U6.13 (-)
unnamed: P_ATN7.2, U7.3 (+)
unnamed: R64.1, R65.2, U7.2 (-)
unnamed: R68.1, U7.6 (-), U7.7
unnamed: R67.2, R68.2, R70.2, R71.1, U7.9 (-)
unnamed: R66.1, R69.2, U7.13 (-)
unnamed: P_ATN8.2, U8.3 (+)
unnamed: R72.1, R73.2, U8.2 (-)
unnamed: R76.1, U8.6 (-), U8.7
unnamed: R75.2, R76.2, R78.2, R79.1, U8.9 (-)
unnamed: R74.1, R77.2, U8.13 (-)
